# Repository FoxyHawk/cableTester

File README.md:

# NS-468 Upgrade

Basic cable tester.

## KiCad Library

Using https://github.com/FoxyHawk/std_lib_SRC

## Untested design

Status :
- [ ] ClockBoard
- [ ] MainBoard
- [ ] SideBoard

## Components

### MainBoard

| Components   | Description     | Quantity |
| ----------   | -----------     | -------- |
| CD4017       | Decimal Counter | 1        |
| PN2222A      | Transistor      | 9        |
| LED          | 2.2V 20mA       | 9        |
| 1N4148       | Diode           | 1        |
| Switch DIP-2 | Switch          | 1        |
| Resistors    | ...             | 18       |
|              | RJ-12 connect   | 1        |
|              | RJ-45 connect   | 1        |

### SideBoard

| Components | Description   | Quantity |
| ---------- | -----------   | -------- |
| LED        | 2.2V 20mA     | 9        |
| 1N4148     | Diode         | 9        |
|            | RJ-12 connect | 1        |
|            | RJ-45 connect | 1        |

### ClockBoard

| Components | Description | Quantity |
| ---------- | ----------- | -------- |
| PN2222A    | Transistor  | 2        |
| LED        | 2.2V 20mA   | 1        |
| Resistors  | ...         | 6        |
| Capacity   | ...         | 1        |

## ToDo List

Test design
Test ClockBoard or change trigger+integrator or NE555 timer

## Simulations

https://www.falstad.com/circuit/

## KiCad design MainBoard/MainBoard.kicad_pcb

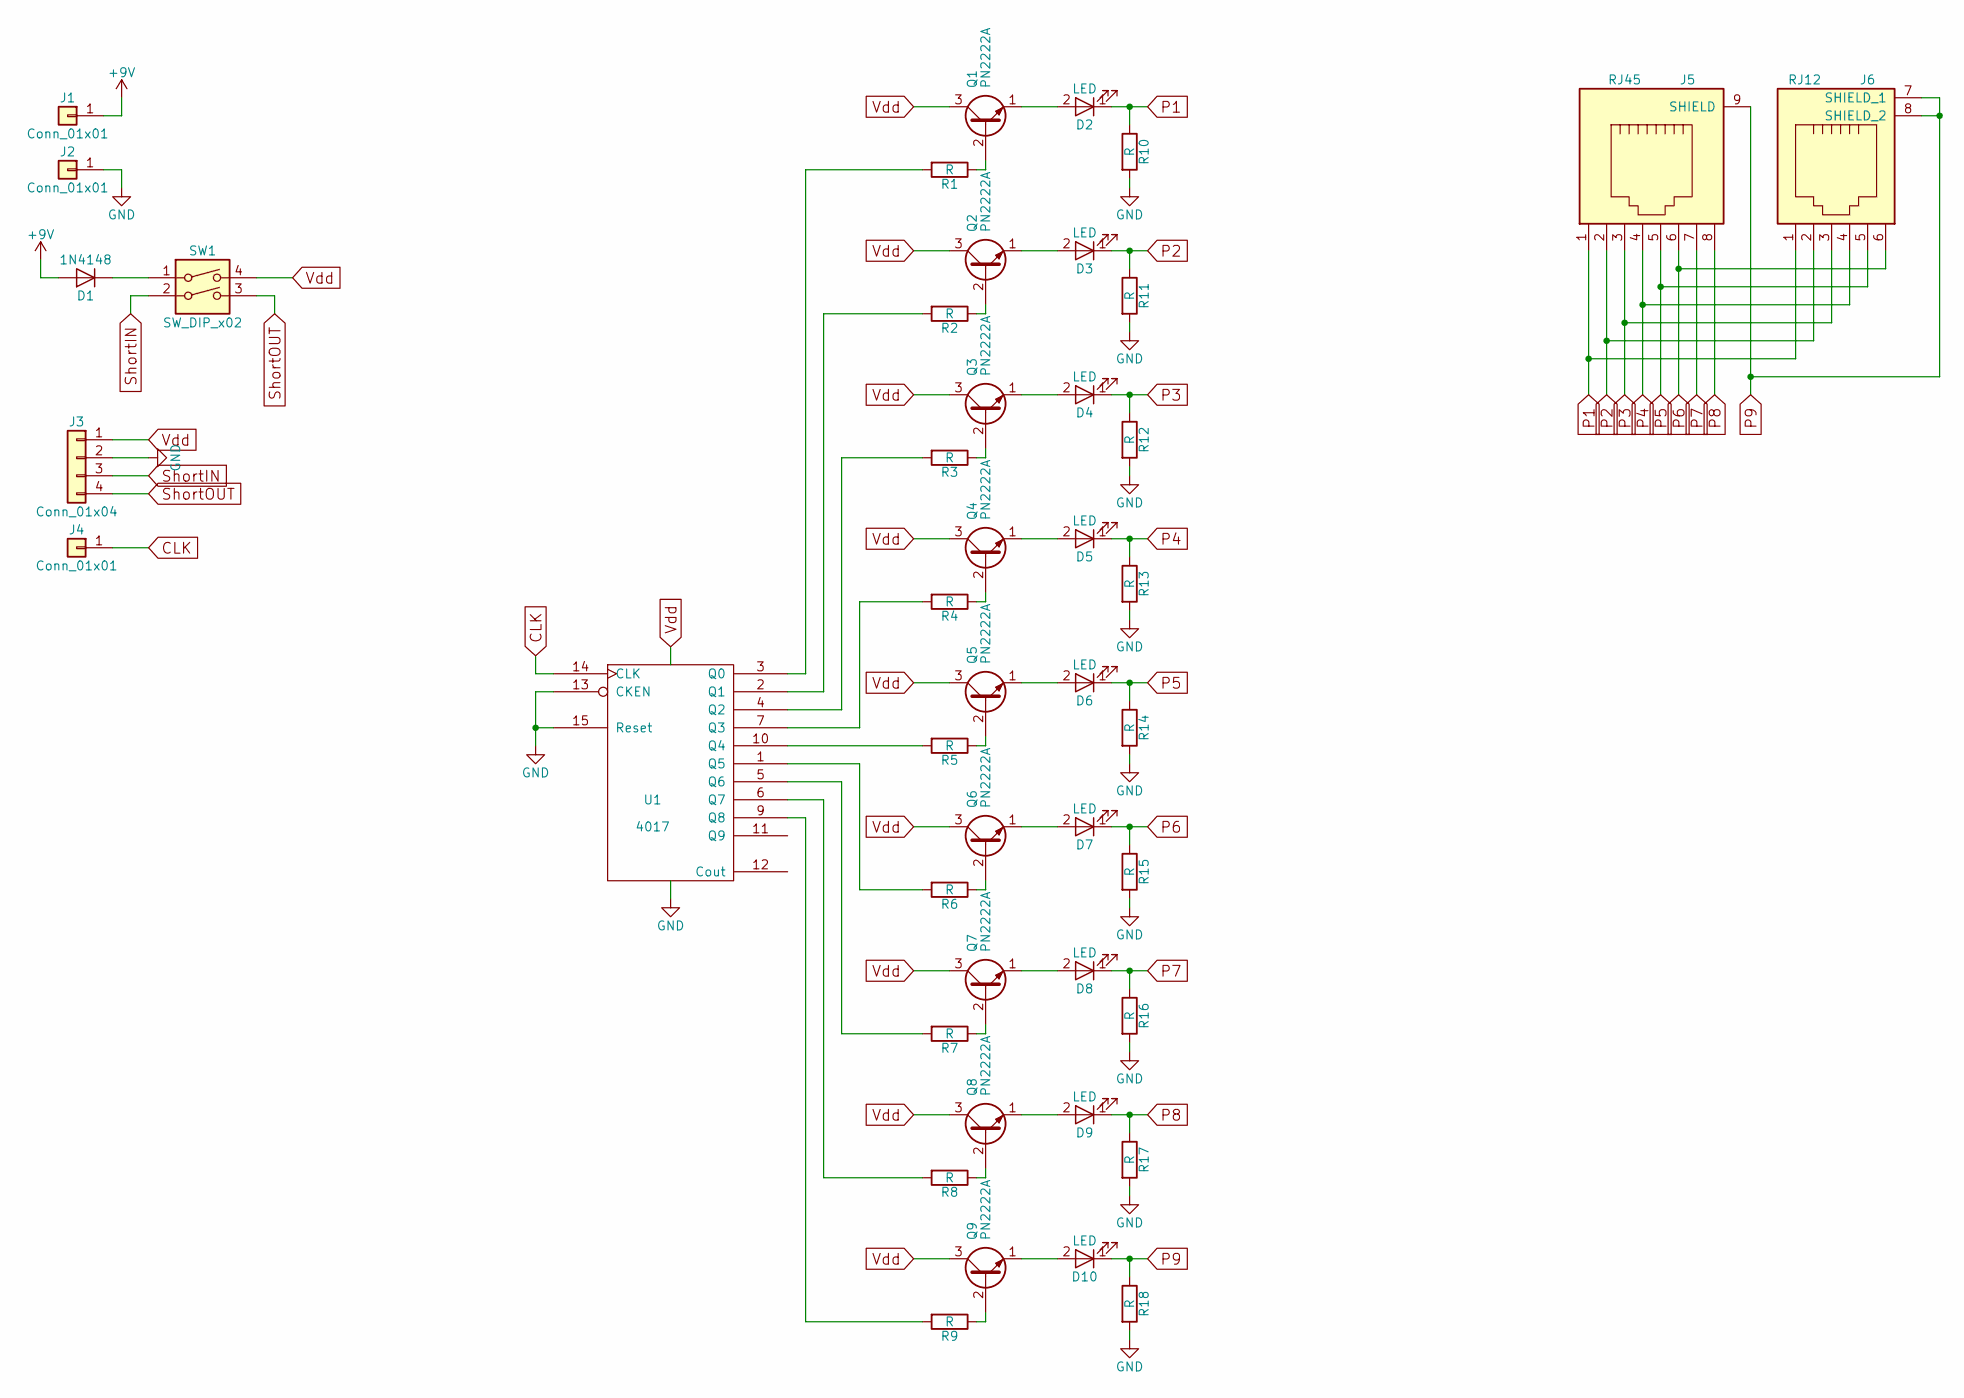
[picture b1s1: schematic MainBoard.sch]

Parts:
D1: 1N4148; Diode
D2, D3, D4, D5, D6, D7, D8, D9, D10: LED; LED_D5.0mm
J1, J2, J4: Conn_01x01; CONN_1x01
J3: Conn_01x04; CONN_1x04
J5: RJ45; RJ45_8_Shield
J6: RJ12; RJ_12
Q1, Q2, Q3, Q4, Q5, Q6, Q7, Q8, Q9: PN2222A; Transistor
R1, R2, R3, R4, R5, R6, R7, R8, R9, R10, R11, R12, R13, R14, R15, R16, R17, R18: R; Resistor
SW1: SW_DIP_x02; DIP-4_W7.62mm
U1: 4017; DIP-16_W7.62mm

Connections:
+9V: D1.2 (A), J1.1
CLK: J4.1, U1.14 (CLK)
GND: J2.1, J3.2, R10.2, R11.2, R12.2, R13.2, R14.2, R15.2, R16.2, R17.2, R18.2, U1.8 (VSS), U1.13 (CKEN), U1.15 (Reset)
unnamed: D1.1 (K), SW1.1
unnamed: D2.2 (A), Q1.1 (E)
unnamed: D3.2 (A), Q2.1 (E)
unnamed: D4.2 (A), Q3.1 (E)
unnamed: D5.2 (A), Q4.1 (E)
unnamed: D6.2 (A), Q5.1 (E)
unnamed: D7.2 (A), Q6.1 (E)
unnamed: D8.2 (A), Q7.1 (E)
unnamed: D9.2 (A), Q8.1 (E)
unnamed: D10.2 (A), Q9.1 (E)
unnamed: Q1.2 (B), R1.1
unnamed: Q2.2 (B), R2.1
unnamed: Q3.2 (B), R3.1
unnamed: Q4.2 (B), R4.1
unnamed: Q5.2 (B), R5.1
unnamed: Q6.2 (B), R6.1
unnamed: Q7.2 (B), R7.1
unnamed: Q8.2 (B), R8.1
unnamed: Q9.2 (B), R9.1
unnamed: R1.2, U1.3 (Q0)
unnamed: R2.2, U1.2 (Q1)
unnamed: R3.2, U1.4 (Q2)
unnamed: R4.2, U1.7 (Q3)
unnamed: R5.2, U1.10 (Q4)
unnamed: R6.2, U1.1 (Q5)
unnamed: R7.2, U1.5 (Q6)
unnamed: R8.2, U1.6 (Q7)
unnamed: R9.2, U1.9 (Q8)
P1: D2.1 (K), J5.1, J6.1, R10.1
P2: D3.1 (K), J5.2, J6.2, R11.1
P3: D4.1 (K), J5.3, J6.3, R12.1
P4: D5.1 (K), J5.4, J6.4, R13.1
P5: D6.1 (K), J5.5, J6.5, R14.1
P6: D7.1 (K), J5.6, J6.6, R15.1
P7: D8.1 (K), J5.7, R16.1
P8: D9.1 (K), J5.8, R17.1
P9: D10.1 (K), J5.9 (SHIELD), J6.7 (SHIELD_1), J6.8 (SHIELD_2), R18.1
ShortIN: J3.3, SW1.2
ShortOUT: J3.4, SW1.3
Vdd: J3.1, Q1.3 (C), Q2.3 (C), Q3.3 (C), Q4.3 (C), Q5.3 (C), Q6.3 (C), Q7.3 (C), Q8.3 (C), Q9.3 (C), SW1.4, U1.16 (VDD)

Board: 2 copper layers, 45 parts (0 on the bottom side), 43 nets, no tracks yet.

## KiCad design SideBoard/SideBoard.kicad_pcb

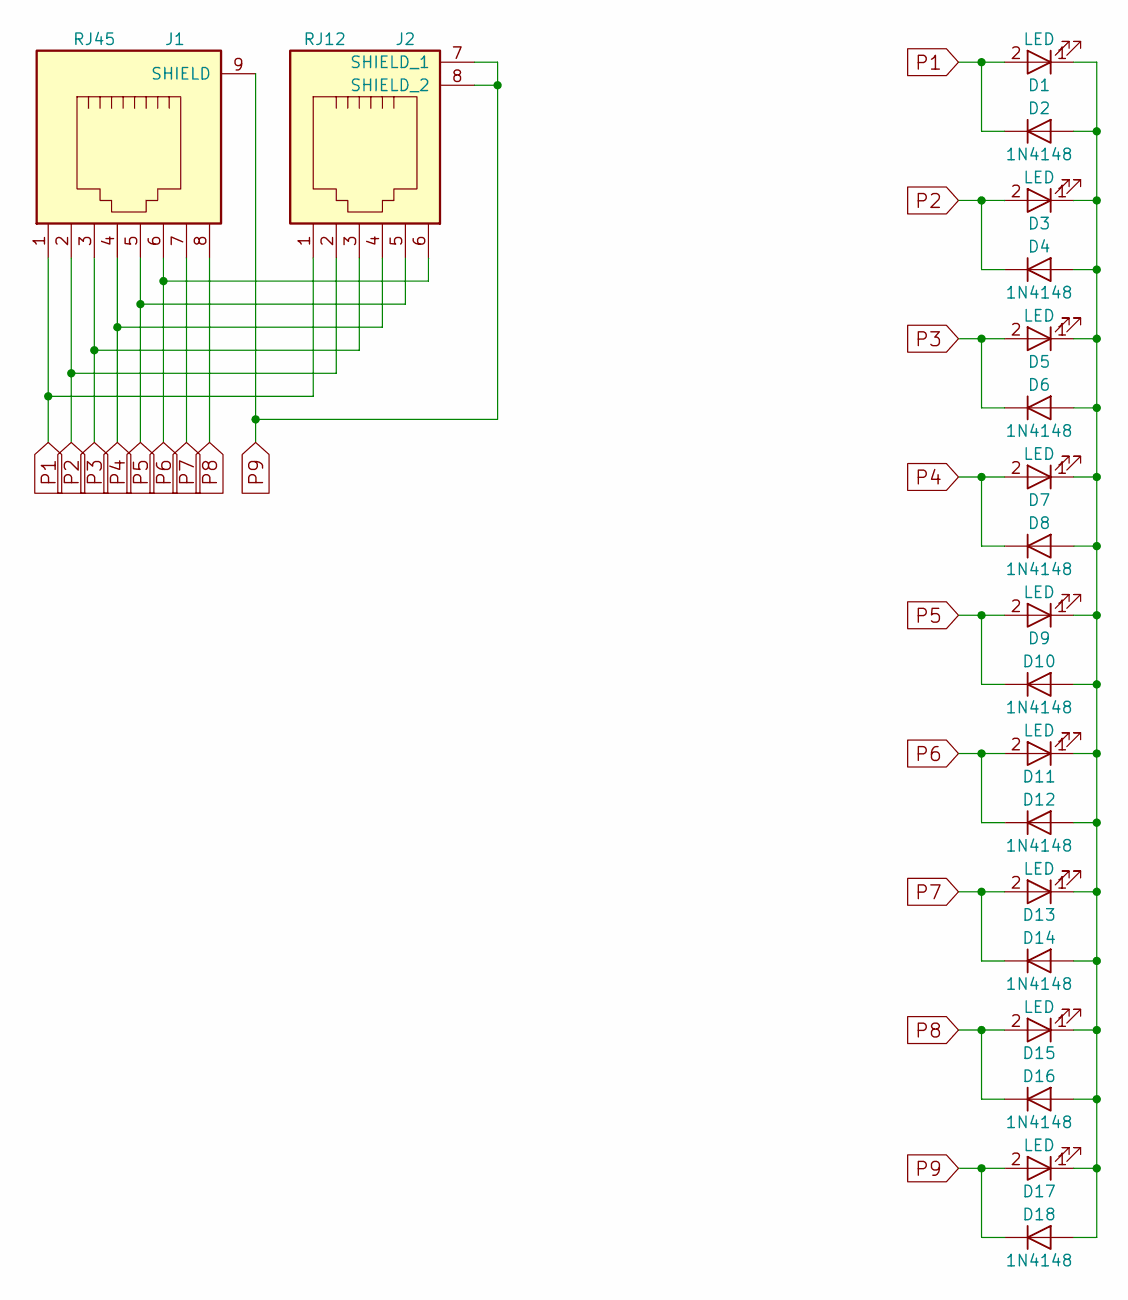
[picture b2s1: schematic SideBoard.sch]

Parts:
D1, D3, D5, D7, D9, D11, D13, D15, D17: LED; LED_D5.0mm
D2, D4, D6, D8, D10, D12, D14, D16, D18: 1N4148; Diode
J1: RJ45; RJ45_8_Shield
J2: RJ12; RJ_12

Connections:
unnamed: D1.1 (K), D2.2 (A), D3.1 (K), D4.2 (A), D5.1 (K), D6.2 (A), D7.1 (K), D8.2 (A), D9.1 (K), D10.2 (A), D11.1 (K), D12.2 (A), D13.1 (K), D14.2 (A), D15.1 (K), D16.2 (A), D17.1 (K), D18.2 (A)
P1: D1.2 (A), D2.1 (K), J1.1, J2.1
P2: D3.2 (A), D4.1 (K), J1.2, J2.2
P3: D5.2 (A), D6.1 (K), J1.3, J2.3
P4: D7.2 (A), D8.1 (K), J1.4, J2.4
P5: D9.2 (A), D10.1 (K), J1.5, J2.5
P6: D11.2 (A), D12.1 (K), J1.6, J2.6
P7: D13.2 (A), D14.1 (K), J1.7
P8: D15.2 (A), D16.1 (K), J1.8
P9: D17.2 (A), D18.1 (K), J1.9 (SHIELD), J2.7 (SHIELD_1), J2.8 (SHIELD_2)

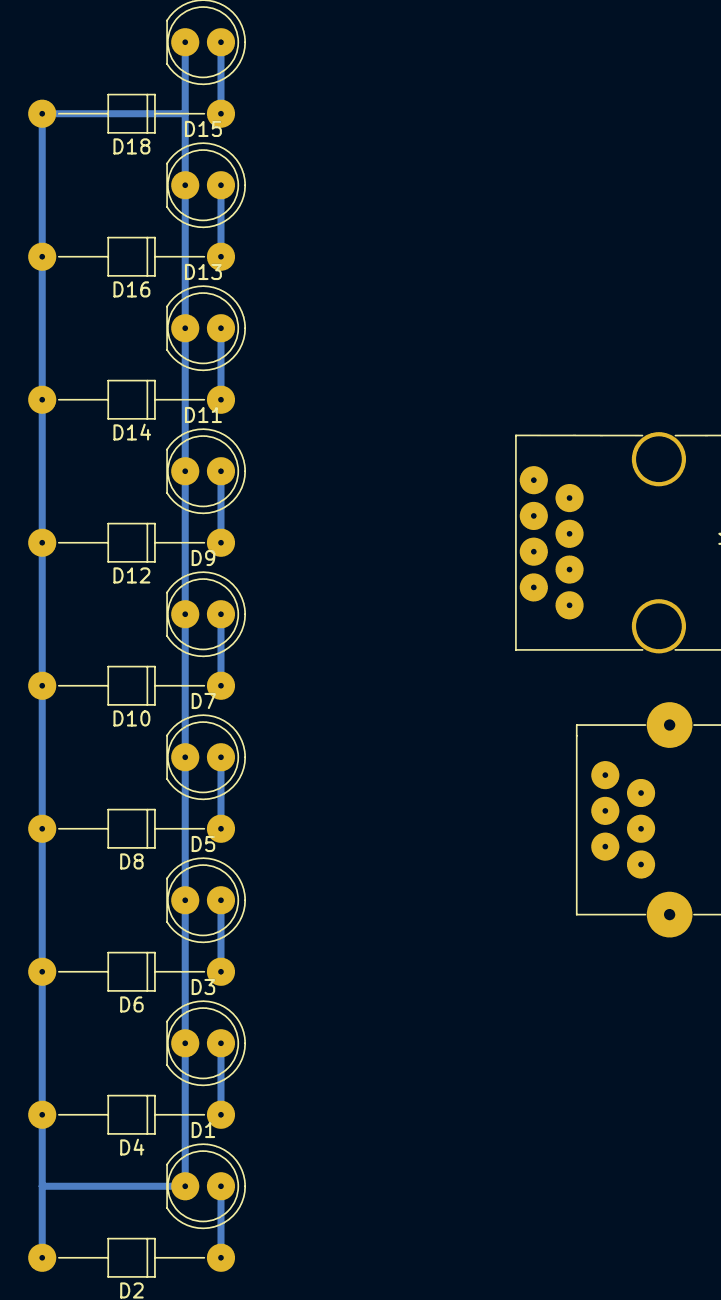
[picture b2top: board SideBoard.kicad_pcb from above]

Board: 2 copper layers, 20 parts (0 on the bottom side), 10 nets.

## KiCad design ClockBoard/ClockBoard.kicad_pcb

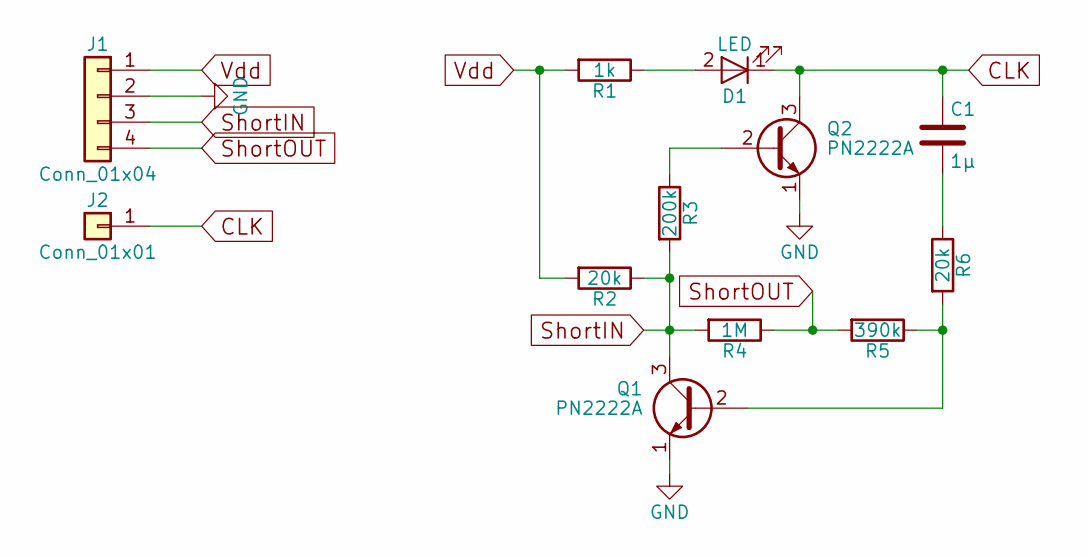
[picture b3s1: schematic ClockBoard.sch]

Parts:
C1: 1µ; C_Rect_W4.0mm
D1: LED; LED_D5.0mm
J1: Conn_01x04; CONN_1x04
J2: Conn_01x01; CONN_1x01
Q1, Q2: PN2222A; Transistor
R1: 1k; Resistor
R2, R6: 20k; Resistor
R3: 200k; Resistor
R4: 1M; Resistor
R5: 390k; Resistor

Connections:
CLK: C1.1, D1.1 (K), J2.1, Q2.3 (C)
GND: J1.2, Q1.1 (E), Q2.1 (E)
unnamed: C1.2, R6.1
unnamed: D1.2 (A), R1.1
unnamed: Q1.2 (B), R5.1, R6.2
unnamed: Q2.2 (B), R3.1
ShortIN: J1.3, Q1.3 (C), R2.1, R3.2, R4.2
ShortOUT: J1.4, R4.1, R5.2
Vdd: J1.1, R1.2, R2.2

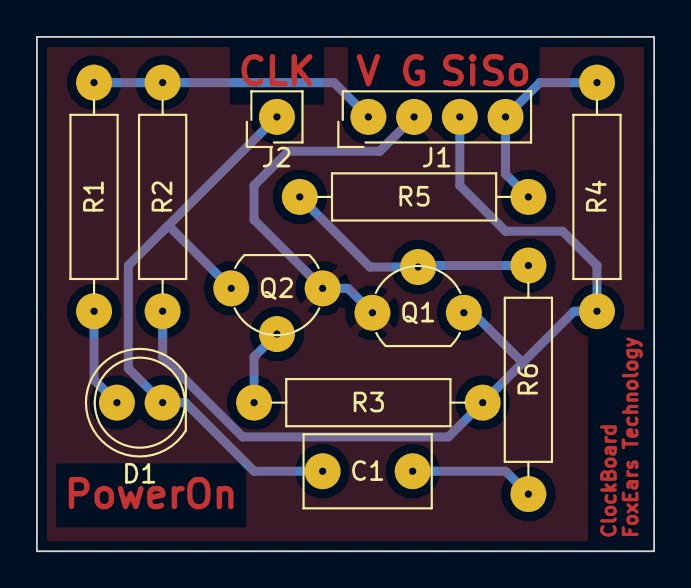
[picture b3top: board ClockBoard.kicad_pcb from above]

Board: 2 copper layers, 34.3 x 28.6 mm, 12 parts (0 on the bottom side), 9 nets.

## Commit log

2018-07-03 Init
2018-07-03 Add README.md
2018-07-03 ClockBoard Routed
2018-07-03 Correct mistakes on SideBoard + begin routing
2018-07-03 List Components
2018-07-03 Correct MainBoard Components
2018-07-03 Change to GNUv3
2018-07-03 Add simulations
2018-07-03 More Licensing
2018-07-04 Update metadata
2018-07-04 Update footprints
